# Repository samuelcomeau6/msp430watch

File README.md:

# msp430watch

These are the source and design files for my MSP430 based wrist watch.

See https://hackaday.io/project/163005-msp430fr5994-based-wrist-watch for project write up and documentation.

This project was designed for me to personally learn more about electronics design and embedded software design. As such, there are guaranteed to be bugs, issues and things that can be improved. I recommend not taking any of my instructions or designs at face value. However, I do have a working device so I must of done something right.

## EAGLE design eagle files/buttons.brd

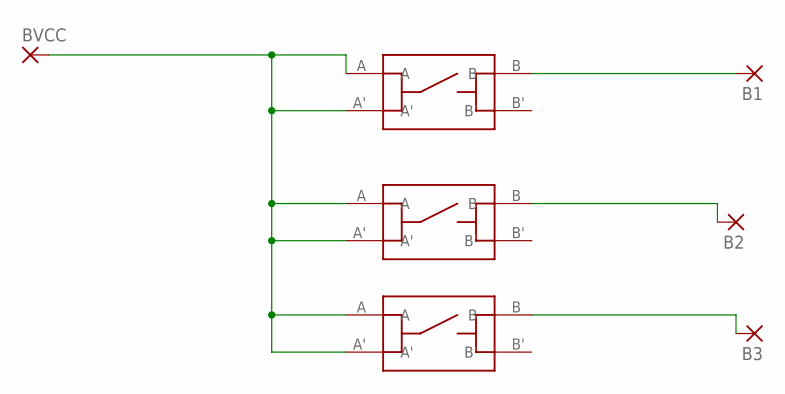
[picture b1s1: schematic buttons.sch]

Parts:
B1, B2, B3: 1,6/0,8
BVCC: 1,6/0,8
U$1, U$2, U$3: EVPBB; EVPVBB

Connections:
unnamed: BVCC.1, U$1.A, U$1.A', U$2.A, U$2.A', U$3.A, U$3.A'
unnamed: B1.1, U$1.B
unnamed: B3.1, U$3.B
unnamed: B2.1, U$2.B

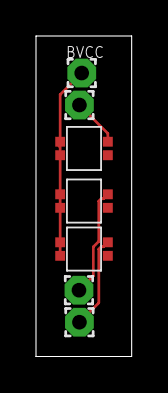
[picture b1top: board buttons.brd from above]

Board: 2 copper layers, 5.3 x 17.8 mm, 7 parts (0 on the bottom side), 4 nets.

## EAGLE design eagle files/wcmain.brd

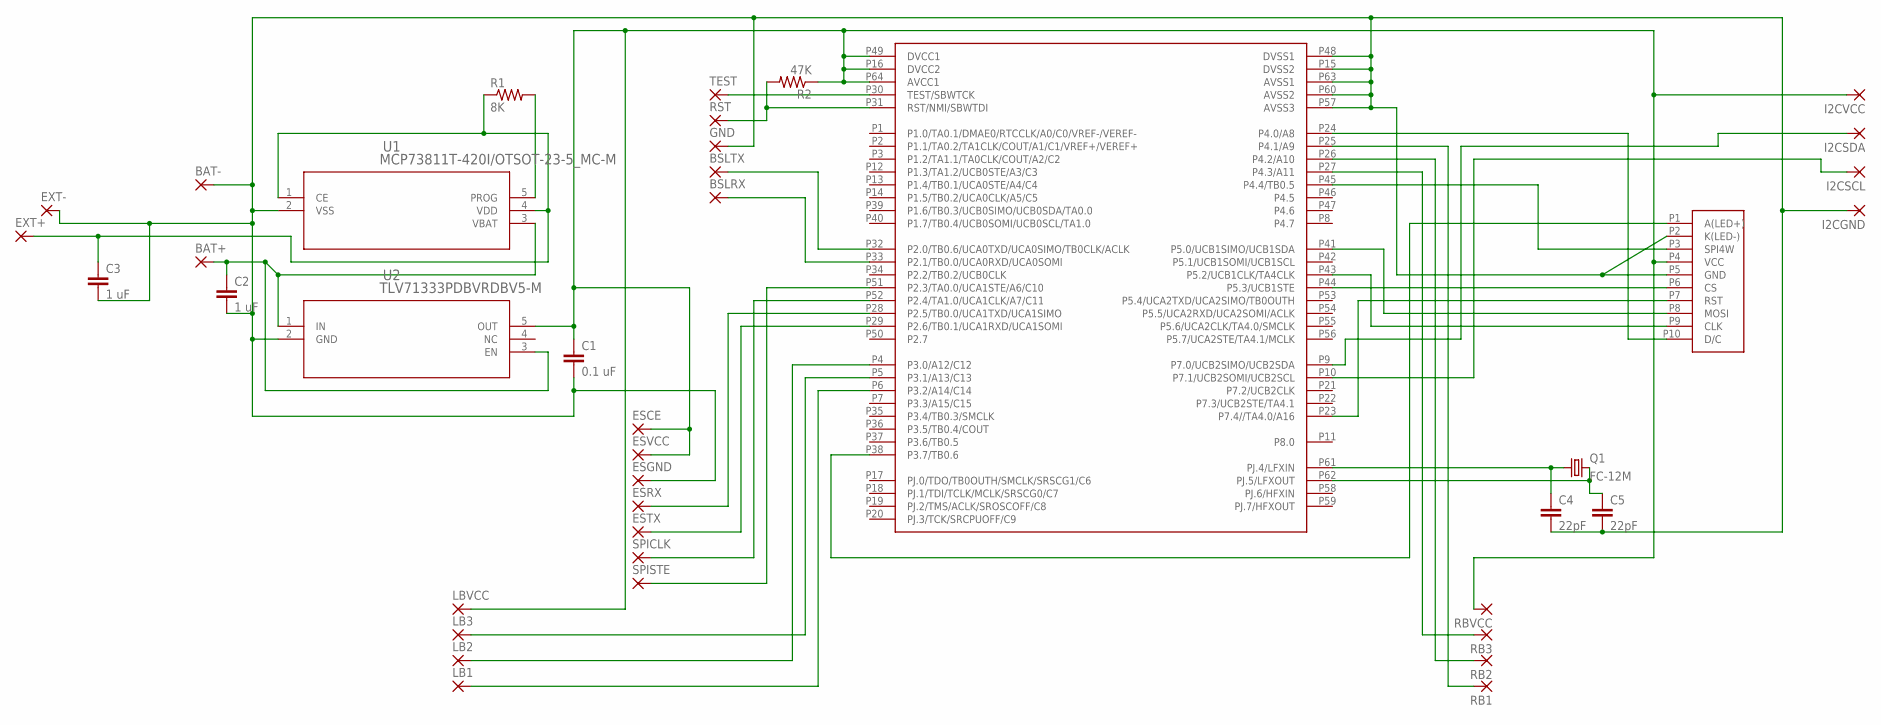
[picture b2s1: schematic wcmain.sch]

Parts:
BAT+: 1,6/0,8
BAT-: 1,6/0,8
BSLRX: 1,6/0,8
BSLTX: 1,6/0,8
C1: 0.1 uF; C0805
C2, C3: 1 uF; C0805
C4, C5: 22pF; C0805
ESCE: 1,6/0,8
ESGND: 1,6/0,8
ESRX: 1,6/0,8
ESTX: 1,6/0,8
ESVCC: 1,6/0,8
EXT+: 1,6/0,8
EXT-: 1,6/0,8
GND: 1,6/0,8
I2CGND, I2CSCL, I2CSDA, I2CVCC: 1,6/0,8
LB1, LB2, LB3: 1,6/0,8
LBVCC: 1,6/0,8
Q1: FC-12M
R1: 8K; R0402
R2: 47K; R0402
RB1, RB2, RB3: 1,6/0,8
RBVCC: 1,6/0,8
RST: 1,6/0,8
SPICLK: 1,6/0,8
SPISTE: 1,6/0,8
TEST: 1,6/0,8
U1: MCP73811T-420I/OTSOT-23-5_MC-M; SOT-23-5_MC-M
U2: TLV71333PDBVRDBV5-M; DBV5-M
U$1: MSP430FR5994PM; PM
U$2: 1-775333-0; 1-1775333-0

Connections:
EXT+: C3.1, EXT+.1, R1.1, U1.1 (CE), U1.4 (VDD)
GND: BAT-.1, C1.2, C2.2, C3.2, C4.2, C5.2, ESGND.1, EXT-.1, GND.1, I2CGND.1, U1.2 (VSS), U2.2 (GND), U$1.P15 (DVSS2), U$1.P48 (DVSS1), U$1.P57 (AVSS3), U$1.P60 (AVSS2), U$1.P63 (AVSS1), U$2.P2 (K(LED-)), U$2.P5 (GND)
unnamed: SPICLK.1, U$1.P52 (P2.4/TA1.0/UCA1CLK/A7/C11)
unnamed: R2.2, RST.1, U$1.P31 (RST/NMI/SBWTDI)
unnamed: SPISTE.1, U$1.P51 (P2.3/TA0.0/UCA1STE/A6/C10)
unnamed: U$1.P41 (P5.0/UCB1SIMO/UCB1SDA), U$2.P8 (MOSI)
unnamed: U$1.P43 (P5.2/UCB1CLK/TA4CLK), U$2.P9 (CLK)
unnamed: U$1.P24 (P4.0/A8), U$2.P10 (D/C)
unnamed: U$1.P23 (P7.4//TA4.0/A16), U$2.P7 (RST)
unnamed: U$1.P44 (P5.3/UCB1STE), U$2.P6 (CS)
unnamed: U$1.P38 (P3.7/TB0.6), U$2.P1 (A(LED+))
unnamed: U$1.P45 (P4.4/TB0.5), U$2.P3 (SPI4W)
unnamed: ESRX.1, U$1.P28 (P2.5/TB0.0/UCA1TXD/UCA1SIMO)
unnamed: TEST.1, U$1.P30 (TEST/SBWTCK)
unnamed: C4.1, Q1.1, U$1.P61 (PJ.4/LFXIN)
unnamed: R1.2, U1.5 (PROG)
unnamed: BSLTX.1, U$1.P32 (P2.0/TB0.6/UCA0TXD/UCA0SIMO/TB0CLK/ACLK)
unnamed: BSLRX.1, U$1.P33 (P2.1/TB0.0/UCA0RXD/UCA0SOMI)
unnamed: C5.1, Q1.2, U$1.P62 (PJ.5/LFXOUT)
unnamed: ESTX.1, U$1.P29 (P2.6/TB0.1/UCA1RXD/UCA1SOMI)
unnamed: LB2.1, U$1.P4 (P3.0/A12/C12)
unnamed: LB3.1, U$1.P5 (P3.1/A13/C13)
unnamed: LB1.1, U$1.P6 (P3.2/A14/C14)
unnamed: RB1.1, U$1.P25 (P4.1/A9)
unnamed: RB2.1, U$1.P26 (P4.2/A10)
unnamed: RB3.1, U$1.P27 (P4.3/A11)
unnamed: I2CSDA.1, U$1.P9 (P7.0/UCB2SIMO/UCB2SDA)
unnamed: I2CSCL.1, U$1.P10 (P7.1/UCB2SOMI/UCB2SCL)
VBAT: BAT+.1, C2.1, U1.3 (VBAT), U2.1 (IN), U2.3 (EN)
VCC: C1.1, ESCE.1, ESVCC.1, I2CVCC.1, LBVCC.1, R2.1, RBVCC.1, U2.5 (OUT), U$1.P16 (DVCC2), U$1.P49 (DVCC1), U$1.P64 (AVCC1), U$2.P4 (VCC)

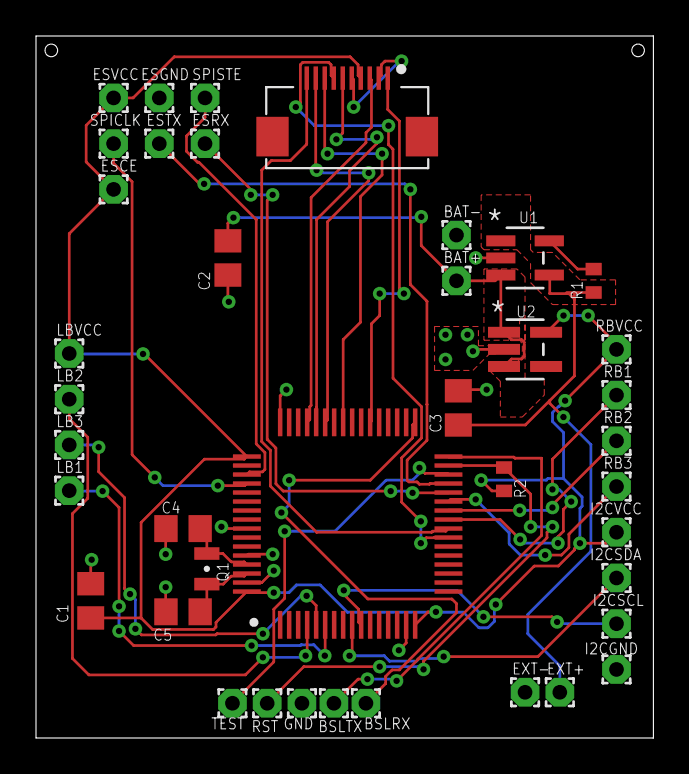
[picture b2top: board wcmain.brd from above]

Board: 2 copper layers, 34.3 x 39.0 mm, 40 parts (0 on the bottom side), 30 nets.

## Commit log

2018-12-28 Added all the files
2020-03-02 Updated Remote to Local
